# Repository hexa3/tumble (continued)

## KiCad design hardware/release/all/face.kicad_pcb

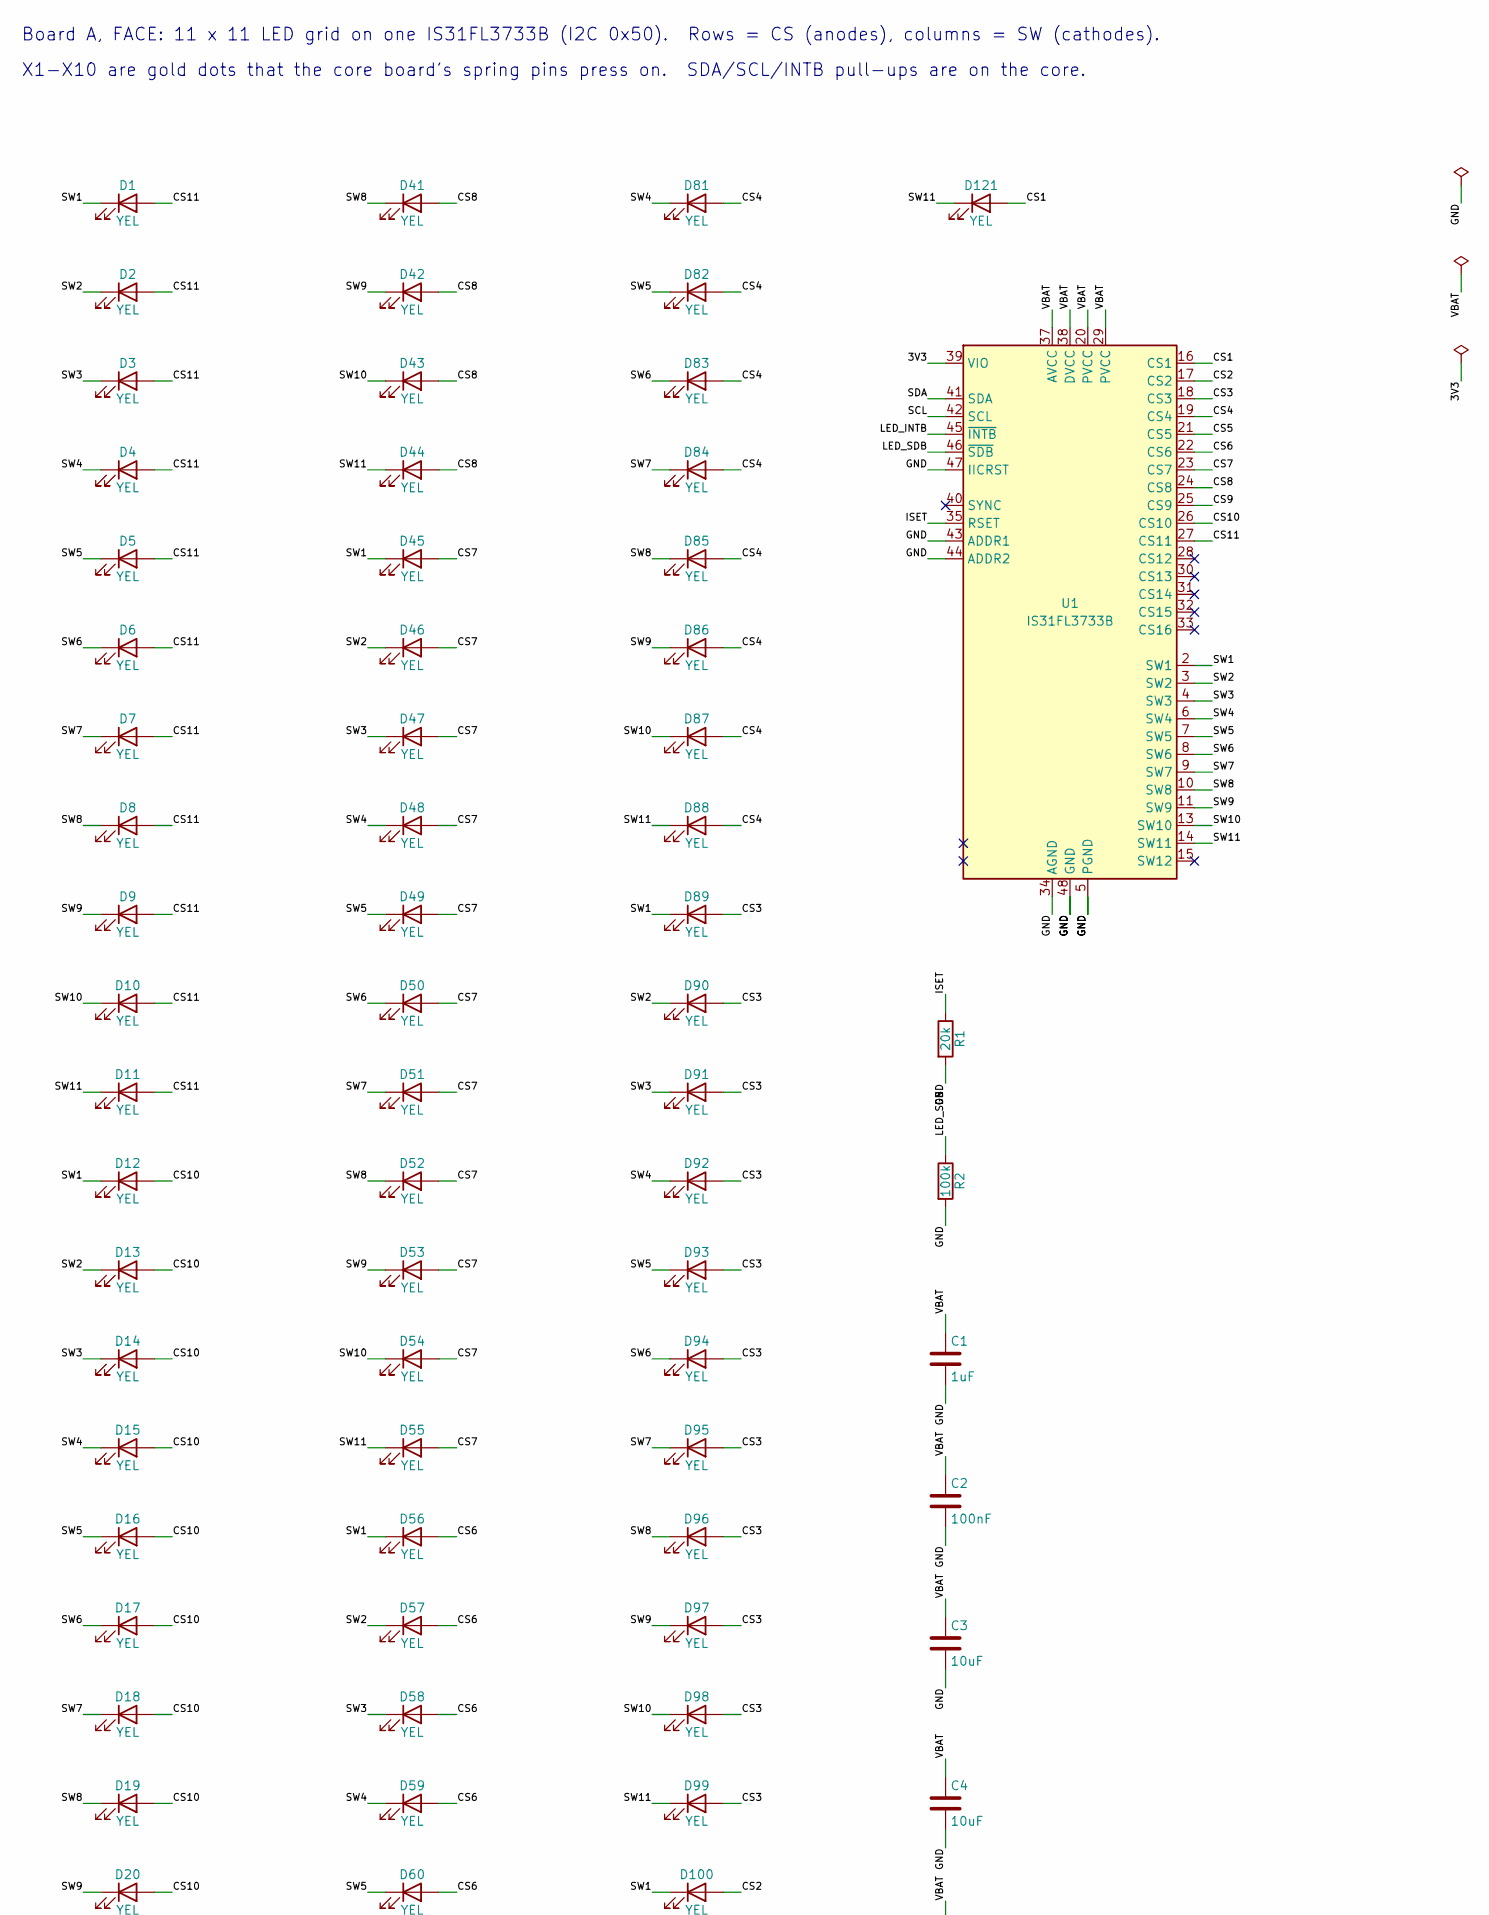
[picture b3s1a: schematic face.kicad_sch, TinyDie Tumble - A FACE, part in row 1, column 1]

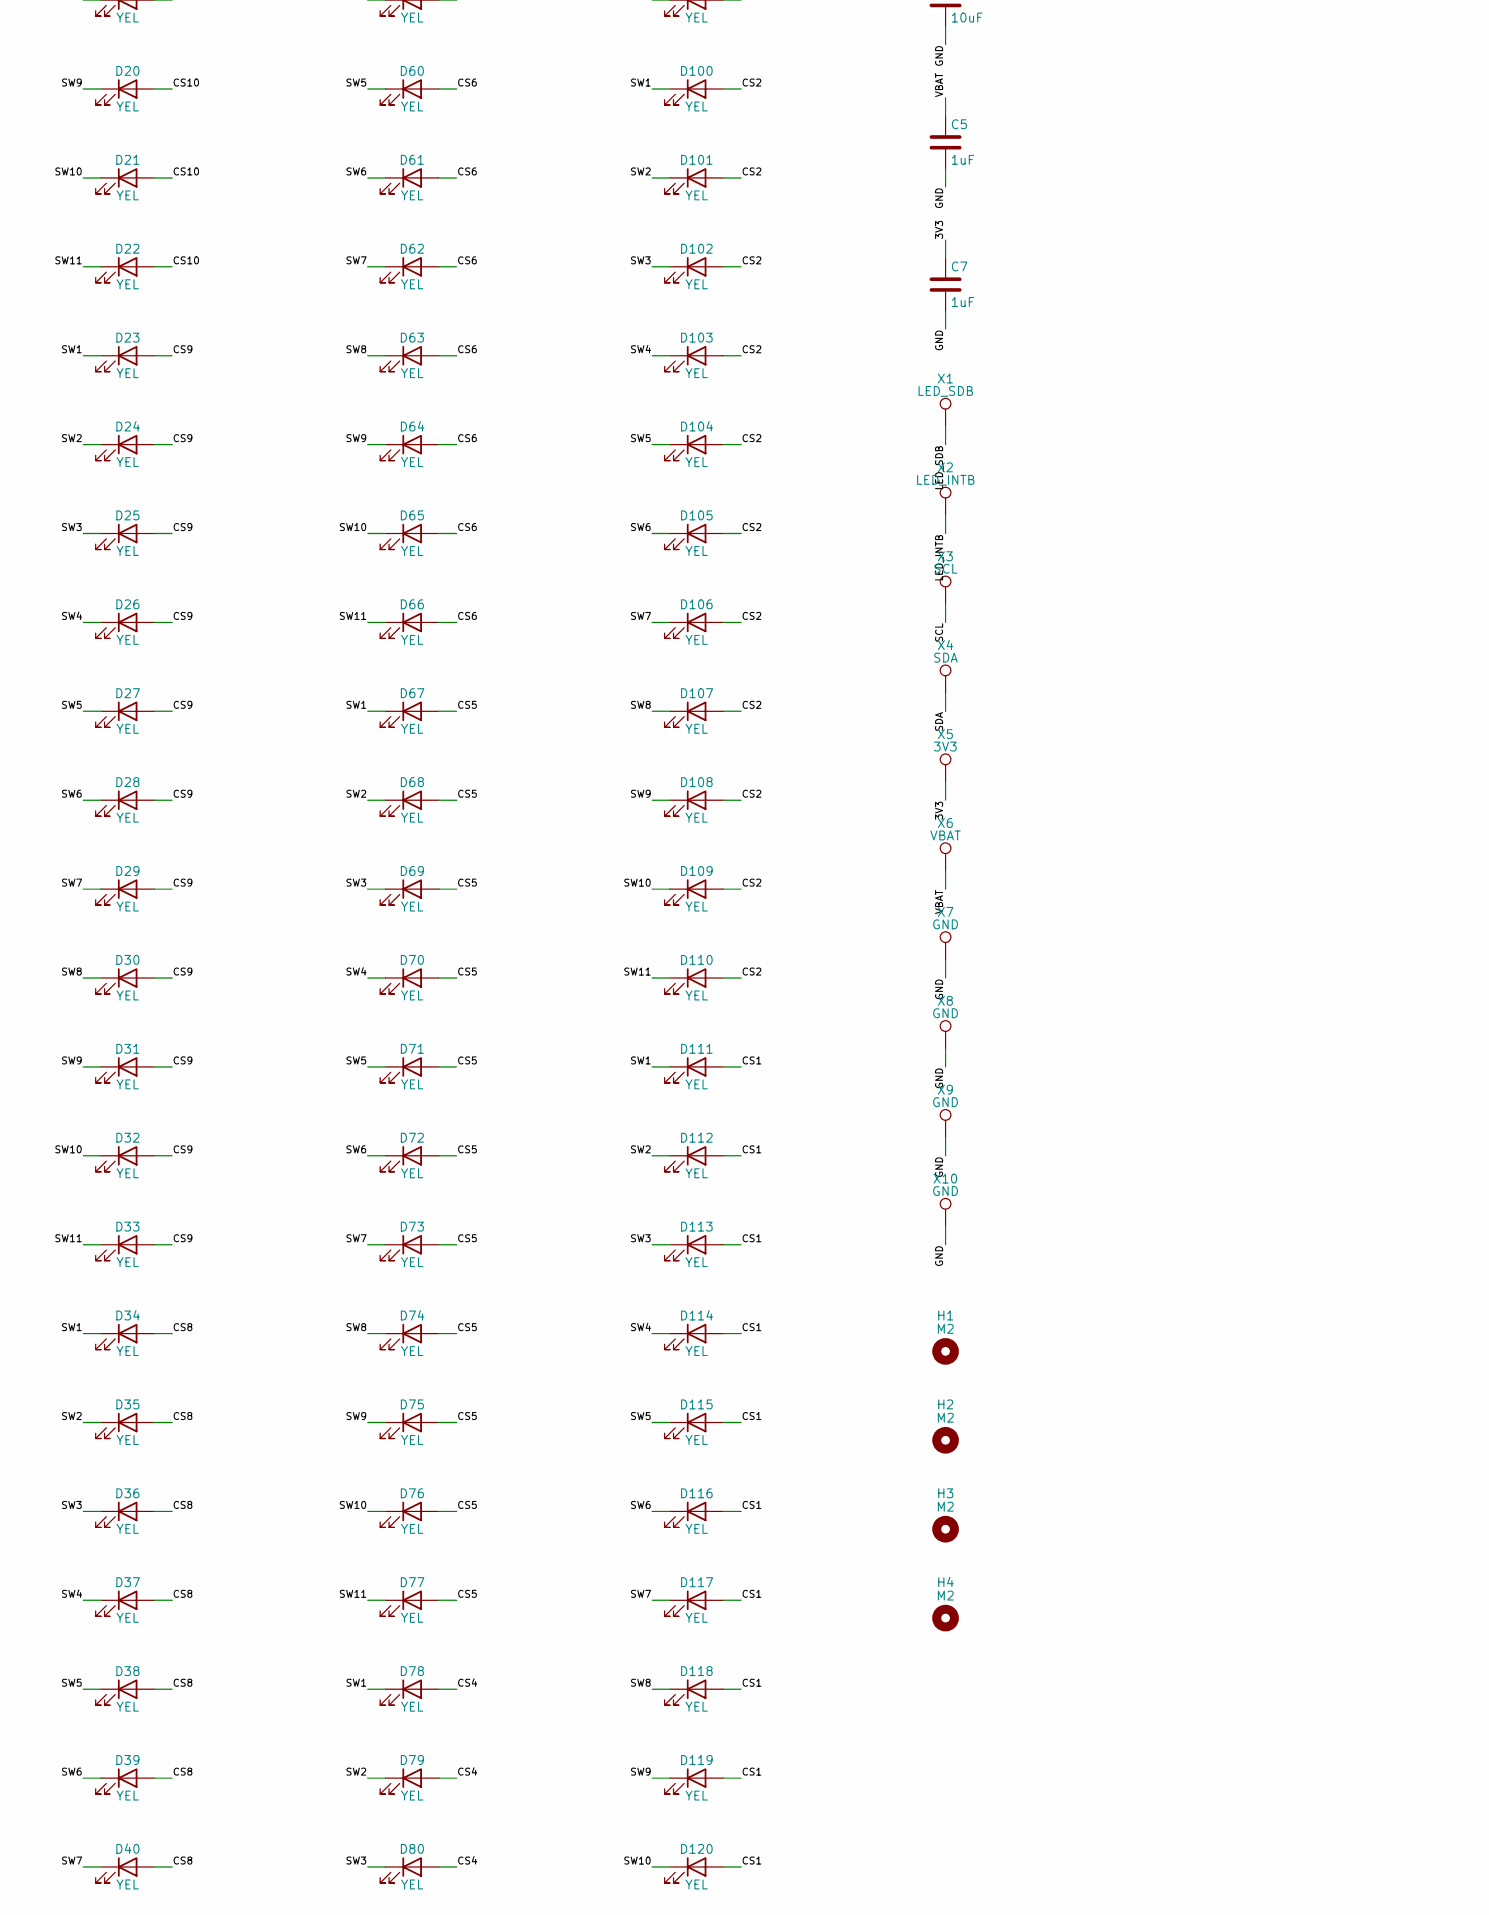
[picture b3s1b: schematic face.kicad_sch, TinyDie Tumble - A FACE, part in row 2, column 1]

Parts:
C1, C5, C7: 1uF; C_0402_1005Metric; MPN CL05A105KA5NQNC; DigiKey_PN 1276-1445-1-ND
C2: 100nF; C_0402_1005Metric; MPN CL05B104KO5NNNC; DigiKey_PN 1276-1001-1-ND
C3, C4: 10uF; C_0603_1608Metric; MPN LMK107BBJ106MALT; DigiKey_PN 587-3258-1-ND
D1, D2, D3, D4, D5, D6, D7, D8, D9, D10, D11, D12, D13, D14, D15, D16, D17, D18, D19, D20, D21, D22, D23, D24, D25, D26, D27, D28, D29, D30, D31, D32, D33, D34, D35, D36, D37, D38, D39, D40, D41, D42, D43, D44, D45, D46, D47, D48, D49, D50, D51, D52, D53, D54, D55, D56, D57, D58, D59, D60, D61, D62, D63, D64, D65, D66, D67, D68, D69, D70, D71, D72, D73, D74, D75, D76, D77, D78, D79, D80, D81, D82, D83, D84, D85, D86, D87, D88, D89, D90, D91, D92, D93, D94, D95, D96, D97, D98, D99, D100, D101, D102, D103, D104, D105, D106, D107, D108, D109, D110, D111, D112, D113, D114, D115, D116, D117, D118, D119, D120, D121: YEL; LED_0402_1005Metric; MPN APHHS1005SYCK; DigiKey_PN 754-1105-1-ND
H1, H2, H3, H4: M2; MountingHole_2.2mm_M2; MPN N/A (PCB copper feature, not a part); DigiKey_PN N/A
R1: 20k; R_0402_1005Metric; MPN RC0402FR-0720KL; DigiKey_PN 311-20.0KLRCT-ND
R2: 100k; R_0402_1005Metric; MPN RC0402FR-07100KL; DigiKey_PN 311-100KLRCT-ND
U1: IS31FL3733B; QFN-48-1EP_6x6mm_P0.4mm_EP4.2x4.2mm; MPN IS31FL3733B-QFLS4-TR; DigiKey_PN TBD (verify)
X1: LED_SDB; PogoLand_D2.2; MPN N/A (PCB copper feature, not a part); DigiKey_PN N/A
X2: LED_INTB; PogoLand_D2.2; MPN N/A (PCB copper feature, not a part); DigiKey_PN N/A
X3: SCL; PogoLand_D2.2; MPN N/A (PCB copper feature, not a part); DigiKey_PN N/A
X4: SDA; PogoLand_D2.2; MPN N/A (PCB copper feature, not a part); DigiKey_PN N/A
X5: 3V3; PogoLand_D2.2; MPN N/A (PCB copper feature, not a part); DigiKey_PN N/A
X6: VBAT; PogoLand_D2.2; MPN N/A (PCB copper feature, not a part); DigiKey_PN N/A
X7, X8, X9, X10: GND; PogoLand_D2.2; MPN N/A (PCB copper feature, not a part); DigiKey_PN N/A

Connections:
/3V3: C7.1, U1.39 (VIO), X5.1
/CS1: D111.2 (A), D112.2 (A), D113.2 (A), D114.2 (A), D115.2 (A), D116.2 (A), D117.2 (A), D118.2 (A), D119.2 (A), D120.2 (A), D121.2 (A), U1.16 (CS1)
/CS2: D100.2 (A), D101.2 (A), D102.2 (A), D103.2 (A), D104.2 (A), D105.2 (A), D106.2 (A), D107.2 (A), D108.2 (A), D109.2 (A), D110.2 (A), U1.17 (CS2)
/CS3: D89.2 (A), D90.2 (A), D91.2 (A), D92.2 (A), D93.2 (A), D94.2 (A), D95.2 (A), D96.2 (A), D97.2 (A), D98.2 (A), D99.2 (A), U1.18 (CS3)
/CS4: D78.2 (A), D79.2 (A), D80.2 (A), D81.2 (A), D82.2 (A), D83.2 (A), D84.2 (A), D85.2 (A), D86.2 (A), D87.2 (A), D88.2 (A), U1.19 (CS4)
/CS5: D67.2 (A), D68.2 (A), D69.2 (A), D70.2 (A), D71.2 (A), D72.2 (A), D73.2 (A), D74.2 (A), D75.2 (A), D76.2 (A), D77.2 (A), U1.21 (CS5)
/CS6: D56.2 (A), D57.2 (A), D58.2 (A), D59.2 (A), D60.2 (A), D61.2 (A), D62.2 (A), D63.2 (A), D64.2 (A), D65.2 (A), D66.2 (A), U1.22 (CS6)
/CS7: D45.2 (A), D46.2 (A), D47.2 (A), D48.2 (A), D49.2 (A), D50.2 (A), D51.2 (A), D52.2 (A), D53.2 (A), D54.2 (A), D55.2 (A), U1.23 (CS7)
/CS8: D34.2 (A), D35.2 (A), D36.2 (A), D37.2 (A), D38.2 (A), D39.2 (A), D40.2 (A), D41.2 (A), D42.2 (A), D43.2 (A), D44.2 (A), U1.24 (CS8)
/CS9: D23.2 (A), D24.2 (A), D25.2 (A), D26.2 (A), D27.2 (A), D28.2 (A), D29.2 (A), D30.2 (A), D31.2 (A), D32.2 (A), D33.2 (A), U1.25 (CS9)
/CS10: D12.2 (A), D13.2 (A), D14.2 (A), D15.2 (A), D16.2 (A), D17.2 (A), D18.2 (A), D19.2 (A), D20.2 (A), D21.2 (A), D22.2 (A), U1.26 (CS10)
/CS11: D1.2 (A), D2.2 (A), D3.2 (A), D4.2 (A), D5.2 (A), D6.2 (A), D7.2 (A), D8.2 (A), D9.2 (A), D10.2 (A), D11.2 (A), U1.27 (CS11)
/GND: C1.2, C2.2, C3.2, C4.2, C5.2, C7.2, R1.2, R2.2, U1.5 (PGND), U1.12 (PGND), U1.34 (AGND), U1.43 (ADDR1), U1.44 (ADDR2), U1.47 (IICRST), U1.48 (GND), U1.49 (GND), X7.1, X8.1, X9.1, X10.1
/ISET: R1.1, U1.35 (RSET)
/LED_INTB: U1.45 (~INTB), X2.1
/LED_SDB: R2.1, U1.46 (~SDB), X1.1
/SCL: U1.42 (SCL), X3.1
/SDA: U1.41 (SDA), X4.1
/SW1: D1.1 (K), D12.1 (K), D23.1 (K), D34.1 (K), D45.1 (K), D56.1 (K), D67.1 (K), D78.1 (K), D89.1 (K), D100.1 (K), D111.1 (K), U1.2 (SW1)
/SW2: D2.1 (K), D13.1 (K), D24.1 (K), D35.1 (K), D46.1 (K), D57.1 (K), D68.1 (K), D79.1 (K), D90.1 (K), D101.1 (K), D112.1 (K), U1.3 (SW2)
/SW3: D3.1 (K), D14.1 (K), D25.1 (K), D36.1 (K), D47.1 (K), D58.1 (K), D69.1 (K), D80.1 (K), D91.1 (K), D102.1 (K), D113.1 (K), U1.4 (SW3)
/SW4: D4.1 (K), D15.1 (K), D26.1 (K), D37.1 (K), D48.1 (K), D59.1 (K), D70.1 (K), D81.1 (K), D92.1 (K), D103.1 (K), D114.1 (K), U1.6 (SW4)
/SW5: D5.1 (K), D16.1 (K), D27.1 (K), D38.1 (K), D49.1 (K), D60.1 (K), D71.1 (K), D82.1 (K), D93.1 (K), D104.1 (K), D115.1 (K), U1.7 (SW5)
/SW6: D6.1 (K), D17.1 (K), D28.1 (K), D39.1 (K), D50.1 (K), D61.1 (K), D72.1 (K), D83.1 (K), D94.1 (K), D105.1 (K), D116.1 (K), U1.8 (SW6)
/SW7: D7.1 (K), D18.1 (K), D29.1 (K), D40.1 (K), D51.1 (K), D62.1 (K), D73.1 (K), D84.1 (K), D95.1 (K), D106.1 (K), D117.1 (K), U1.9 (SW7)
/SW8: D8.1 (K), D19.1 (K), D30.1 (K), D41.1 (K), D52.1 (K), D63.1 (K), D74.1 (K), D85.1 (K), D96.1 (K), D107.1 (K), D118.1 (K), U1.10 (SW8)
/SW9: D9.1 (K), D20.1 (K), D31.1 (K), D42.1 (K), D53.1 (K), D64.1 (K), D75.1 (K), D86.1 (K), D97.1 (K), D108.1 (K), D119.1 (K), U1.11 (SW9)
/SW10: D10.1 (K), D21.1 (K), D32.1 (K), D43.1 (K), D54.1 (K), D65.1 (K), D76.1 (K), D87.1 (K), D98.1 (K), D109.1 (K), D120.1 (K), U1.13 (SW10)
/SW11: D11.1 (K), D22.1 (K), D33.1 (K), D44.1 (K), D55.1 (K), D66.1 (K), D77.1 (K), D88.1 (K), D99.1 (K), D110.1 (K), D121.1 (K), U1.14 (SW11)
/VBAT: C1.1, C2.1, C3.1, C4.1, C5.1, U1.20 (PVCC), U1.29 (PVCC), U1.37 (AVCC), U1.38 (DVCC), X6.1

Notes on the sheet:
Board A, FACE: 11 x 11 LED grid on one IS31FL3733B (I2C 0x50). Rows = CS (anodes), columns = SW (cathodes).
X1-X10 are gold dots that the core board's spring pins press on. SDA/SCL/INTB pull-ups are on the core.

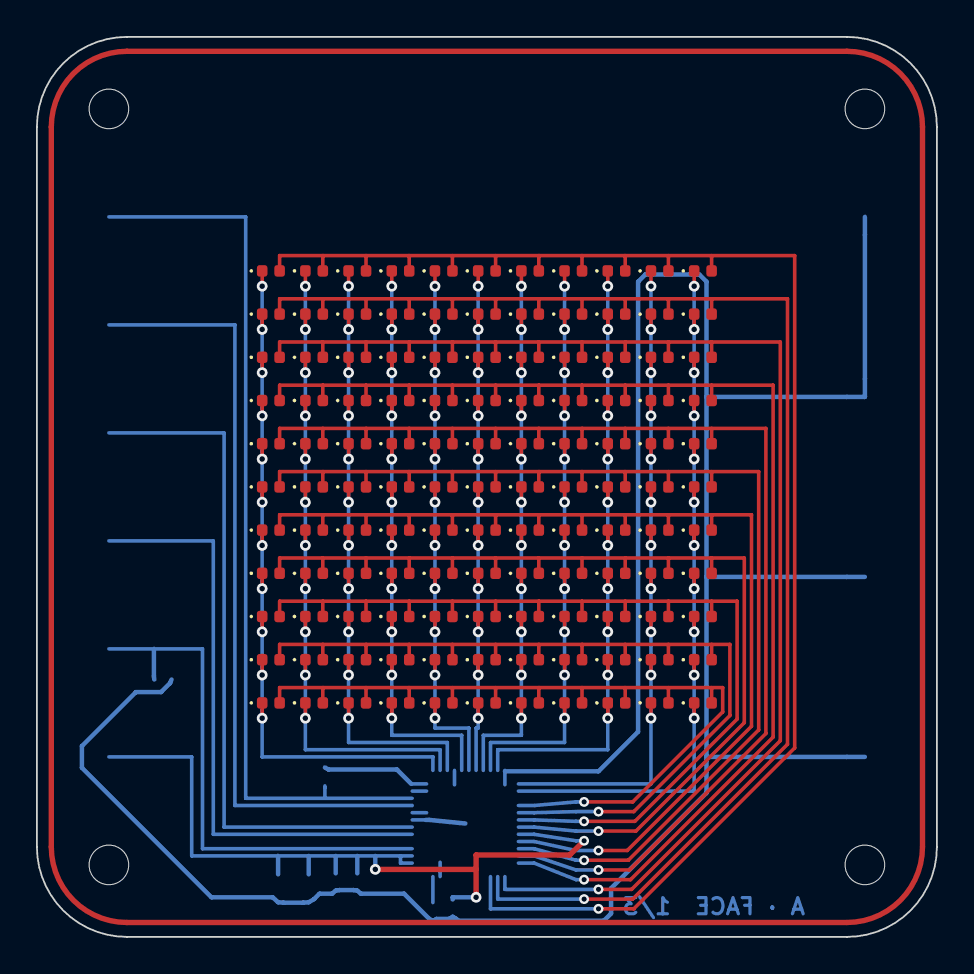
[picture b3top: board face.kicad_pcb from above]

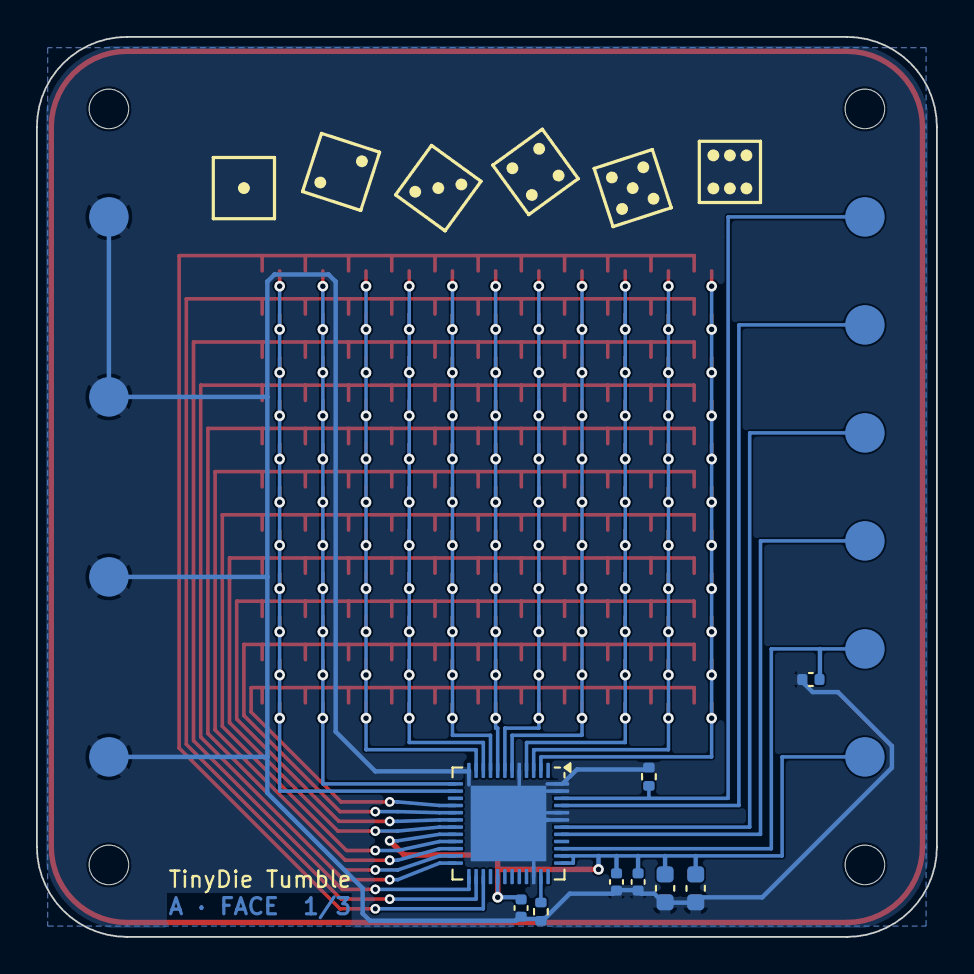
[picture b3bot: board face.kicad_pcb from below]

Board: 2 copper layers, 50.0 x 50.0 mm, 144 parts (19 on the bottom side), 30 nets.

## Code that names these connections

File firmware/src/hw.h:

/* STM32G041J6 (SO-8) hardware layer.  Six I/O pins:
 *   pin 1  PB7   NOISE_ADC (ADC1_IN11)        pin 5  PA9   I2C1_SCL
 *   pin 4  PA2   UART (USART2_TX, half-duplex) pin 6  PA10  I2C1_SDA
 *   pin 7  PA13  SWDIO, then NOISE_EN         pin 8  PA14/PB5  SWCLK, then ACC_INT1 (PB5, EXTI5)
 * hw_init() leaves pins 7 and 8 as SWD; hw_release_swd() (called 2 s after reset) takes them over. */
#ifndef HW_H
#define HW_H
#include <stddef.h>
#include <stdint.h>
#include "i2c_bus.h"

extern const i2c_bus_t hw_i2c;
extern volatile uint32_t hw_ms;

void hw_init(void);
void hw_release_swd(void);
void hw_noise(int on);
void hw_noise_samples(uint16_t *buf, size_t n);
void hw_trng(uint32_t *w, size_t n);
int hw_usb_present(void);           /* the bridge holds the UART line high only while USB is plugged in */
int hw_uart_getc(void);             /* -1 if nothing */
void hw_uart_puts(const char *s);
int hw_acc_int(void);
void hw_sleep(void);                /* STOP1 until the accelerometer interrupt */
void hw_delay_ms(uint32_t ms);
#endif
